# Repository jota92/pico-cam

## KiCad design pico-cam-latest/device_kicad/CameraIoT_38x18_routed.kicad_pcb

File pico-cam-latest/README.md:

# Pico-Cam (Camera IoT)

ESP32-S3 (ESP32-S3-PICO-1-N8R8) をベースにした、超小型・低消費電力の IoT カメラプロジェクトです。ディープスリープを活用し、定期的に JPEG 画像を撮影して Wi-Fi 経由でサーバーにアップロードします。

本リポジトリには、デバイス基板、書き込み・充電用のドック基板の KiCad 回路図・レイアウトデータ、PlatformIO 用のファームウェア、およびアップロード受信用サーバーのサンプルコードが含まれています。

---

## プロジェクト構成

```text
pico-cam/
├── camera_iot/                 # メインの開発・製造パッケージ
│   ├── device_kicad/           # デバイス本体の基板データ (38x18mm 版)
│   ├── cradle_kicad/           # 充電・書き込み用クレードル基板データ (RevA)
│   ├── mechanical/             # デバイスおよびクレードルのレイアウト画像・図面
│   ├── firmware_platformio/    # ESP32-S3 ファームウェア (PlatformIO)
│   ├── server_example/         # アップロード受信用 Express.js サーバー
│   ├── docs/                   # ピンマップや電気設計メモ、DRC レポートなどの設計文書
│   ├── scripts/                # 基板生成や監査用の各種 Python スクリプト
│   ├── jlcpcb_38x18/           # 38x18mm 版の製造用 Gerber/BOM/CPL 出力
│   └── jlcpcb_dock/            # ドック基板の製造用 Gerber/BOM/CPL 出力
├── device_kicad_friend/        # 代替・改良版の基板データ
│   ├── CameraIoT_RevF_40x20_ThroughVia_FINAL.kicad_pcb  # RevF 本体基板 (40x20mm、ブラインドビアなしの通常の4層)
│   ├── CameraIoT_USB-C_Programmer_Dock.kicad_pcb        # USB-C プログラマードック基板
│   └── README_HANDOFF.md       # RevF 基板の製造仕様・引き継ぎドキュメント
├── KiCad/                      # 実行環境用の KiCad 設定 / プロファイル
├── .kicad_cli_profile/         # KiCad CLI 用プロファイル
├── freerouting-1.9.0.jar       # 基板配線用オートルーター (FreeRouting)
└── README.md                   # 本ドキュメント
```

---

## ハードウェア仕様

本プロジェクトには、用途や製造コストに合わせて 2 つの基板バリエーションが存在します。

### 1. デバイス本体基板

*   **ESP32-S3-PICO-1-N8R8**: 8MB Quad Flash & 8MB Octal PSRAM 内蔵モジュール
*   **インターフェース**: カメラモジュール (OV2640 等)、充電検出、ステータス LED、操作ボタン
*   **電源**: LiPo バッテリー接続用コネクタ (J2: JST SH 2ピン)

#### バリエーション:
1.  **38x18mm 版 (`camera_iot/device_kicad/`)**:
    *   極小サイズの設計。
    *   製造用データは `camera_iot/jlcpcb_38x18/` にあります。
2.  **40x20mm RevF 版 (`device_kicad_friend/`)**:
    *   ブラインドビア/埋め込みビアを排除し、通常の「4層貫通ビア (Through-Via)」のみで配線した設計。
    *   JLCPCB などの一般的な基板メーカーで安価に製造可能。
    *   外形寸法: 40.0 x 20.0 mm、基板厚: 0.8 mm。

### 2. 充電・書き込み用ドック (クレードル)

デバイス本体には USB コネクタを搭載せず、外部ドック（ポゴピンまたはケーブル接続）を介して充電やファームウェア書き込みを行います。

*   **Pogo ピンまたは 6-Pin ケーブルインターフェース**:
    1.  `VBUS / VCHG_5V` (電源)
    2.  `GND` (グランド)
    3.  `USB_D+` (native USB D+ / GPIO20)
    4.  `USB_D-` (native USB D- / GPIO19)
    5.  `GPIO0 / BOOT` (書き込みモード遷移用)
    6.  `CHIP_PU / RESET` (チップリセット)
    *   (RevC の pogo 設計では、STAT / WAKE_ID を含めた 8 ポゴピン仕様も存在)

---

## ファームウェア (PlatformIO)

`camera_iot/firmware_platformio/` に格納されているファームウェアは、ESP32-S3 の native USB 機能と Wi-Fi 機能、省電力制御を実装しています。

### ピンアサイン (Pin Map)
*   **PSRAM 競合回避**: ESP32-S3-PICO-1-N8R8 は Octal PSRAM のために `GPIO33~37` を占有するため、カメラのデータラインを `GPIO10-14`、`GPIO38-40` にマッピングして競合を回避しています。
*   **主要ピン**:
    *   `PWDN_GPIO_NUM`: GPIO21
    *   `RESET_GPIO_NUM`: GPIO18
    *   `XCLK_GPIO_NUM`: GPIO15
    *   `SIOD_GPIO_NUM` (SDA): GPIO8
    *   `SIOC_GPIO_NUM` (SCL): GPIO9
    *   `Y2 ~ Y9` (カメラデータ D2~D9): GPIO40, 39, 38, 14, 13, 12, 11, 10
    *   `VSYNC_GPIO_NUM`: GPIO16
    *   `HREF_GPIO_NUM`: GPIO17
    *   `PCLK_GPIO_NUM`: GPIO41
    *   `LED_STATUS_GPIO`: GPIO47 (ステータス LED)
    *   `CHG_DETECT_GPIO`: GPIO4 (充電検出ピン、分圧経由)
    *   `WAKE_BUTTON_GPIO`: GPIO5 (操作・スリープ解除ボタン)
    *   `WAKE_ID_GPIO`: GPIO1 (クレードル接続識別)
    *   `USB_DN_GPIO / USB_DP_GPIO`: GPIO19 / GPIO20 (Native USB デバッグ・書き込み用)

### 主な動作フロー:
1.  **起動**: スリープまたは電源 ON で起動。
2.  **充電検出**: `CHG_DETECT_GPIO` が HIGH の場合（ドックで充電中など）、不要なカメラ撮影や Wi-Fi 接続を行わず、充電に専念するために即座に 1 分間のディープスリープに入ります。
3.  **撮影**: カメラを初期化し、JPEG 画像を取得して PSRAM に格納。
4.  **Wi-Fi 送信**: Wi-Fi に接続し、指定された HTTP サーバへ POST リクエストで画像を送信。
5.  **休止**: 送信完了（またはタイムアウト/エラー）後、ステータス LED をパターン点滅させ、10 分間のディープスリープに入ります。

---

## サーバー (server_example)

`camera_iot/server_example/` は Node.js (Express.js) で書かれたシンプルなアップロード受付サーバーです。

*   **動作**: 送信されてきた Raw JPEG データをトークン認証の上で受信し、日時とランダム文字列のファイル名（例: `2026-06-20T01-23-57-123Z-abcd1234.jpg`）で `./uploads` ディレクトリに保存します。
*   **起動方法**:
    ```bash
    cd camera_iot/server_example
    npm install
    # トークンやポートを指定して起動
    PORT=3000 DEVICE_TOKEN="your-secret-token" node server.js
    ```

---

## 開発と製造に関する注意点

*   **BOM の手配**: LCSC などの自動 PCBA を利用する場合、カメラコネクタや一部の IC など、手作業でのマウント (PCBA 後の手半田) が必要な部品が存在します。詳細は `camera_iot/docs/manual_procurement_revC.md` や `device_kicad_friend/README_HANDOFF.md` をご確認ください。
*   **DRC（デザインルールチェック）**:
    *   RevF 基板は KiCad 10.0.1 の DRC にて、重大なエラー・未配線ともに 0 件であることを確認済みです。

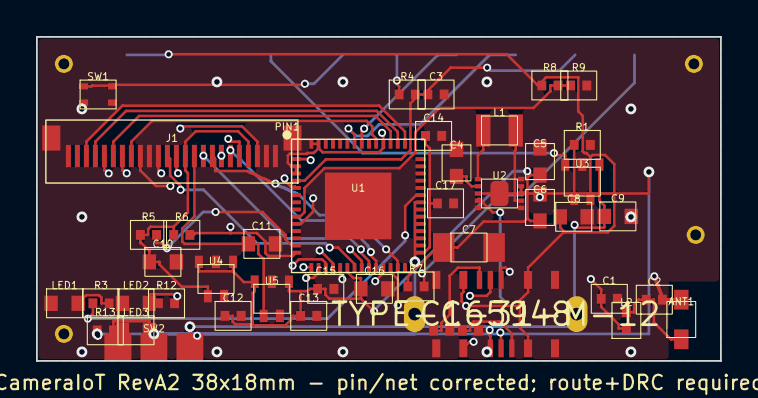
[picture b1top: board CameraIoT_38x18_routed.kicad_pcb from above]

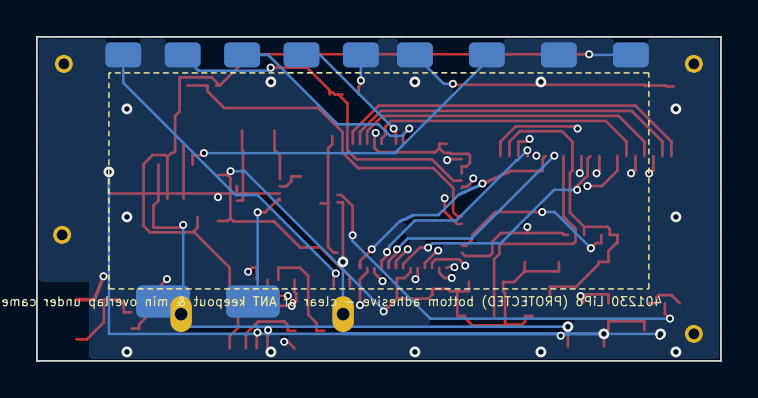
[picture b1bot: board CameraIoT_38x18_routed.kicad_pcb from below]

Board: 4 copper layers, 38.0 x 18.0 mm, 59 parts (11 on the bottom side), 45 nets.

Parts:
ANT1: 2.4GHz chip antenna; ANT_2450AT18B100E
BAT+: BAT+; BATP
BAT-: BAT-; BATN
C1, C2: DNP RF shunt; C_0402_1005Metric
C3, C12, C13: 1uF; C_0402_1005Metric
C4, C5, C6: 10uF 6.3V; C_0603_1608Metric
C7: 47uF 6.3V; C_1206_3216Metric
C8, C10, C16: 10uF; C_0603_1608Metric
C9, C11: 4.7uF; C_0603_1608Metric
C14, C15, C17: 0.1uF; C_0402_1005Metric
J1: OV2640 24pin FPC; FPC_24P_0.5mm_Molex52437-2491
J2: USB-C power+USB2; CameraIoT_USB-C-16P
L1: 1.5uH >=1.5A; IND_2520
L2: 0R/DNP RF series; R_0402_1005Metric
LED1: Blue status LED; LED_0603_1608Metric
LED2: Red Power LED; LED_0603_1608Metric
LED3: Green WiFi LED; LED_0603_1608Metric
MH1: MH1
MH2: MH2
MH3: MH3
MH4: MH4
R1: 20k 1%; R_0402_1005Metric
R3, R12, R13: 1k; R_0402_1005Metric
R4, R5, R6, R7: 10k; R_0402_1005Metric
R8: 68k; R_0402_1005Metric
R9: 100k; R_0402_1005Metric
R10: 5.11k CC1; R_0402
R11: 5.11k CC2; R_0402
SW1: Wake/Boot button; SW_2x1.6mm
SW2: Power Switch
TP1: 5V; BottomPad_5V
TP2: GND; BottomPad_GND
TP3: STAT; BottomPad_STAT
TP4: WAKE; BottomPad_WAKE
TP5: 3V3; BottomPad_3V3
TP6: TX; BottomPad_TX
TP7: RX; BottomPad_RX
TP8: EN; BottomPad_EN
TP9: IO0; BottomPad_IO0
U1: ESP32-S3-PICO-1-N8R8; LGA56_7x7mm_P0.4_PIN1TL
U2: 3.3V buck-boost; VSON10_2.5x2.5_DSK
U3: LiPo charger 4.2V; SOT-23-5
U4: 2.8V LDO; SOT-23-5
U5: 1.3V LDO; SOT-23-5

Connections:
1V3: C11.1, J1.10, U5.5
2V8: C10.1, J1.4, J1.11, R5.1, R6.1, U4.5
3V3: C5.1, C6.1, C7.1, C12.1, C13.1, C15.1, C16.1, R4.1, R7.1, R12.1, TP5.1, U1.2, U1.3, U1.20, U1.46, U1.55, U1.56, U2.8, U2.9, U4.1, U4.3, U5.1, U5.3
CAM_D2: J1.19, U1.45
CAM_D3: J1.21, U1.44
CAM_D4: J1.22, U1.43
CAM_D5: J1.20, U1.19
CAM_D6: J1.18, U1.18
CAM_D7: J1.16, U1.17
CAM_D8: J1.14, U1.16
CAM_D9: J1.12, U1.15
CAM_HREF: J1.9, U1.23
CAM_PCLK: J1.17, U1.47
CAM_PWDN: J1.8, U1.27
CAM_RESETB: J1.6, U1.24
CAM_SIOC: J1.5, R6.2, U1.14
CAM_SIOD: J1.3, R5.2, U1.13
CAM_VSYNC: J1.7, U1.22
CAM_XCLK: J1.13, U1.21
CC1: J2.A5, R10.1
CC2: J2.B5, R11.1
CHG_DETECT: R8.2, R9.1, U1.9
CHG_PROG: R1.1, U3.5
CHG_STAT: TP3.1, U3.1
CHIP_PU: C3.1, R4.2, TP8.1, U1.4
GND: ANT1.2, BAT-.1, C1.2, C2.2, C3.2, C4.2, C5.2, C6.2, C7.2, C8.2, C9.2, C10.2, C11.2, C12.2, C13.2, C14.2, C15.2, C16.2, C17.2, J1.2, J1.15, J1.S1, J1.S2, J2.A1, J2.A12, J2.B1, J2.B12, J2.S1, J2.S2, LED1.1, LED2.1, LED3.1, R1.2, R9.2, R10.2, R11.2, SW1.3, SW1.4, SW2.1, TP2.1, U1.57, U2.5, U2.6, U2.10, U2.11, U3.2, U4.2, U5.2
GPIO0: R7.2, TP9.1, U1.5
LED_A: LED1.2, R3.2
LED_PWR_A: LED2.2, R12.2
LED_STATUS: R3.1, U1.37
LED_WIFI: R13.1, U1.36
LED_WIFI_A: LED3.2, R13.2
LNA_IN: C1.1, L2.1, U1.1
RF_ANT: ANT1.1, C2.1, L2.2
TPS_EN: SW2.2, U2.3
TPS_L1: L1.1, U2.1
TPS_L2: L1.2, U2.7
U0RXD: TP7.1, U1.50
U0TXD: TP6.1, U1.49
USB_DN: J2.A7, J2.B7, U1.25
USB_DP: J2.A6, J2.B6, U1.26
VBAT: BAT+.1, C4.1, C9.1, SW2.3, U2.2, U2.4, U3.3
VCHG_5V: C8.1, J2.A4, J2.A9, J2.B4, J2.B9, R8.1, TP1.1, U3.4
VDD_SPI: C14.1, C17.1, U1.29
WAKE_BUTTON: SW1.1, SW1.2, TP4.1, U1.10

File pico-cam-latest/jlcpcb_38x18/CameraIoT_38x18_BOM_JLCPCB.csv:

Comment,Designator,Footprint,Manufacturer,Manufacturer Part Number,LCSC Part #,Quantity,Notes
2.4GHz chip antenna,ANT1,ANT_2450AT18B100E,Johanson Technology,2450AT18B100E,C2917717,1,JLCPCB SMT
10uF,"C10,C16,C8",C_0603_1608Metric,Samsung,CL10A106MQ8NNNC,C19702,3,JLCPCB SMT
4.7uF,"C11,C9",C_0603_1608Metric,Samsung,CL10A475KO8NNNC,C19666,2,JLCPCB SMT
1uF,"C12,C13,C3",C_0402_1005Metric,Samsung,CL05A105KA5NQNC,C52923,3,JLCPCB SMT
0.1uF,"C14,C15,C17",C_0402_1005Metric,Samsung,CL05B104KO5NNNC,C1525,3,JLCPCB SMT
10uF 6.3V,"C4,C5,C6",C_0603_1608Metric,Samsung,CL10A106MQ8NNNC,C19702,3,JLCPCB SMT
47uF 6.3V,C7,C_1206_3216Metric,Samsung,CL31A476MQHNNNE,C2013,1,JLCPCB SMT
OV2640 24pin FPC,J1,FPC_24P_0.5mm_Molex52437-2491,Molex,52437-2471,C3169564,1,JLCPCB SMT
USB-C power+USB2,J2,CameraIoT_USB-C-16P,,TYPE-C-31-M-12,C165948,1,JLCPCB SMT
1.5uH >=1.5A,L1,IND_2520,Murata,DFE252012F-1R5M=P2,C909806,1,JLCPCB SMT
0R/DNP RF series,L2,R_0402_1005Metric,UNI-ROYAL,0402WGF0000TCE,C17168,1,JLCPCB SMT
Blue status LED,LED1,LED_0603_1608Metric,Everlight,19-21/BHC-ZL1M2VY/3T,C2290,1,JLCPCB SMT
20k 1%,R1,R_0402_1005Metric,UNI-ROYAL,0402WGF2002TCE,C25741,1,JLCPCB SMT
5.11k CC1,R10,R_0402,UNI-ROYAL,0402WGF1001TCE,C21190,1,JLCPCB SMT
5.11k CC2,R11,R_0402,UNI-ROYAL,0402WGF1001TCE,C21190,1,JLCPCB SMT
1k,R3,R_0402_1005Metric,UNI-ROYAL,0402WGF1001TCE,C21190,1,JLCPCB SMT
10k,"R4,R5,R6,R7",R_0402_1005Metric,UNI-ROYAL,0402WGF1002TCE,C25744,4,JLCPCB SMT
68k,R8,R_0402_1005Metric,Yageo,RC0402FR-0768KL,C25907,1,JLCPCB SMT
100k,R9,R_0402_1005Metric,UNI-ROYAL,0402WGF1003TCE,C25803,1,JLCPCB SMT
Wake/Boot button,SW1,SW_2x1.6mm,ALPS Alpine,SKRPACE010,C139797,1,JLCPCB SMT
ESP32-S3-PICO-1-N8R8,U1,LGA56_7x7mm_P0.4_PIN1TL,Espressif,ESP32-S3-PICO-1-N8R8,C7545129,1,JLC SMT/consign
3.3V buck-boost,U2,VSON10_2.5x2.5_DSK,Texas Instruments,TPS63031DSKR,C15516,1,JLCPCB SMT
LiPo charger 4.2V,U3,SOT-23-5,Microchip,MCP73831T-2ACI/OT,C424093,1,JLCPCB SMT
2.8V LDO,U4,SOT-23-5,Texas Instruments,TLV70028DDCR,C507266,1,JLCPCB SMT
1.3V LDO,U5,SOT-23-5,Texas Instruments,TLV70013DDCR,TLV70013DDCR,1,JLC SMT/consign

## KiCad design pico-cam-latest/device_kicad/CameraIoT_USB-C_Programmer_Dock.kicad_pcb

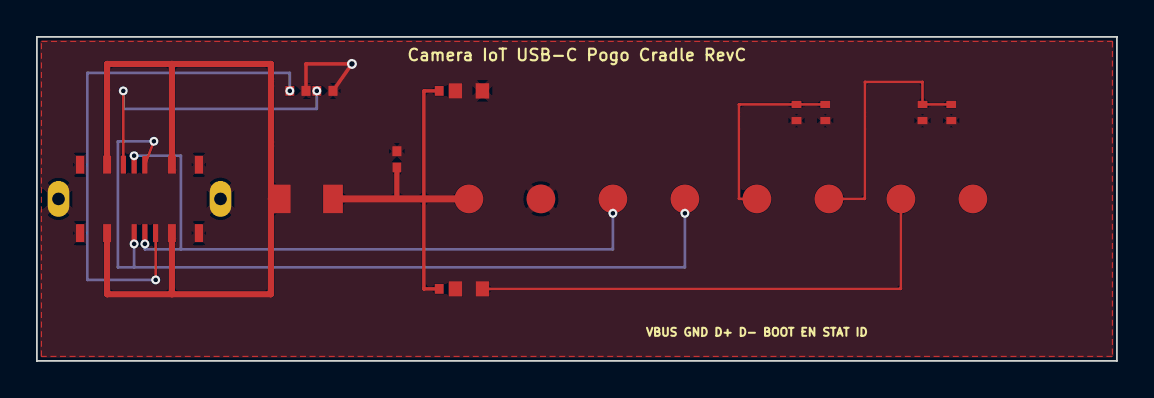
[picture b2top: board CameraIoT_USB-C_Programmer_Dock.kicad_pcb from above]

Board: 2 copper layers, 60.0 x 18.0 mm, 19 parts (0 on the bottom side), 12 nets.

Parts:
D1: 5V TVS; SOD-523
F1: 500mA PTC; Fuse_1206
J1: USB-C power+USB2; CameraIoT_USB-C-16P
LED1: Power LED; LED_0603
LED2: Charge LED; LED_0603
P1: Pogo VBUS; CameraIoT_PogoPad_1.6
P2: Pogo GND; CameraIoT_PogoPad_1.6
P3: Pogo D+; CameraIoT_PogoPad_1.6
P4: Pogo D-; CameraIoT_PogoPad_1.6
P5: Pogo BOOT; CameraIoT_PogoPad_1.6
P6: Pogo RESET; CameraIoT_PogoPad_1.6
P7: Pogo STAT; CameraIoT_PogoPad_1.6
P8: Pogo WAKE/ID; CameraIoT_PogoPad_1.6
R1, R2: 5.1k; R_0402
R3, R4: 2.2k; R_0402
SW2: FLASH button; CameraIoT_SKRPACE010
SW3: RESET button; CameraIoT_SKRPACE010

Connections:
CC1: J1.A5, R1.1
CC2: J1.B5, R2.1
CHG_LED_A: LED2.1, R4.2
CHIP_PU: P6.1, SW3.1, SW3.2
GND: D1.2, J1.A1, J1.A12, J1.B1, J1.B12, J1.S1, J1.S2, LED1.2, P2.1, R1.2, R2.2, SW2.3, SW2.4, SW3.3, SW3.4
GPIO0: P5.1, SW2.1, SW2.2
PWR_LED: LED1.1, R3.2
STAT: LED2.2, P7.1
USB_DN: J1.A7, J1.B7, P4.1
USB_DP: J1.A6, J1.B6, P3.1
VBUS_5V: F1.1, J1.A4, J1.A9, J1.B4, J1.B9
VBUS_PROTECTED: D1.1, F1.2, P1.1, R3.1, R4.1

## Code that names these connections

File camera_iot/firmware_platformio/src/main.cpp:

#include <Arduino.h>
#include <WiFi.h>
#include <HTTPClient.h>
#include "esp_camera.h"

// CameraIoT RevC pin map.
// ESP32-S3-PICO-1-N8R8 reserves GPIO33-37 for octal PSRAM.
// GPIO19/20 are reserved for USB_D-/USB_D+ via the pogo cradle.
// The user button stays on GPIO5; cradle ID is split out to GPIO1.
#define PWDN_GPIO_NUM     21
#define RESET_GPIO_NUM    18
#define XCLK_GPIO_NUM     15
#define SIOD_GPIO_NUM      8
#define SIOC_GPIO_NUM      9
#define Y9_GPIO_NUM       10  // D9 MSB  (was 33 - PSRAM conflict)
#define Y8_GPIO_NUM       11  //         (was 34 - PSRAM conflict)
#define Y7_GPIO_NUM       12  //         (was 35 - PSRAM conflict)
#define Y6_GPIO_NUM       13  //         (was 36 - PSRAM conflict)
#define Y5_GPIO_NUM       14  //         (was 37 - PSRAM conflict)
#define Y4_GPIO_NUM       38
#define Y3_GPIO_NUM       39
#define Y2_GPIO_NUM       40  // D2 LSB
#define VSYNC_GPIO_NUM    16
#define HREF_GPIO_NUM     17
#define PCLK_GPIO_NUM     41

#define LED_STATUS_GPIO   47
#define CHG_DETECT_GPIO    4
#define WAKE_BUTTON_GPIO   5
#define WAKE_ID_GPIO       1
#define USB_DN_GPIO       19
#define USB_DP_GPIO       20

// Fill these in before flashing.
static const char* WIFI_SSID = "YOUR_WIFI_SSID";
static const char* WIFI_PASS = "YOUR_WIFI_PASSWORD";
static const char* UPLOAD_URL = "https://your-server.example.com/upload";
static const char* DEVICE_TOKEN = "replace-with-device-token";

static void blink(int n) {
  pinMode(LED_STATUS_GPIO, OUTPUT);
  for (int i=0; i<n; ++i) { digitalWrite(LED_STATUS_GPIO, HIGH); delay(100); digitalWrite(LED_STATUS_GPIO, LOW); delay(100); }
}

static bool init_camera() {
  camera_config_t config;
  config.ledc_channel = LEDC_CHANNEL_0;
  config.ledc_timer = LEDC_TIMER_0;
  config.pin_d0 = Y2_GPIO_NUM;
  config.pin_d1 = Y3_GPIO_NUM;
  config.pin_d2 = Y4_GPIO_NUM;
  config.pin_d3 = Y5_GPIO_NUM;
  config.pin_d4 = Y6_GPIO_NUM;
  config.pin_d5 = Y7_GPIO_NUM;
  config.pin_d6 = Y8_GPIO_NUM;
  config.pin_d7 = Y9_GPIO_NUM;
  config.pin_xclk = XCLK_GPIO_NUM;
  config.pin_pclk = PCLK_GPIO_NUM;
  config.pin_vsync = VSYNC_GPIO_NUM;
  config.pin_href = HREF_GPIO_NUM;
  config.pin_sccb_sda = SIOD_GPIO_NUM;
  config.pin_sccb_scl = SIOC_GPIO_NUM;
  config.pin_pwdn = PWDN_GPIO_NUM;
  config.pin_reset = RESET_GPIO_NUM;
  config.xclk_freq_hz = 20000000;
  config.pixel_format = PIXFORMAT_JPEG;

  if (psramFound()) {
    config.frame_size = FRAMESIZE_SVGA;  // 800x600 first test. Lower to VGA/QVGA if unstable.
    config.jpeg_quality = 12;
    config.fb_count = 2;
    config.grab_mode = CAMERA_GRAB_LATEST;
  } else {
    config.frame_size = FRAMESIZE_VGA;
    config.jpeg_quality = 14;
    config.fb_count = 1;
    config.grab_mode = CAMERA_GRAB_WHEN_EMPTY;
  }
  config.fb_location = CAMERA_FB_IN_PSRAM;

  esp_err_t err = esp_camera_init(&config);
  if (err != ESP_OK) {
    Serial.printf("Camera init failed: 0x%x\n", err);
    return false;
  }
  sensor_t *s = esp_camera_sensor_get();
  if (s) {
    s->set_framesize(s, FRAMESIZE_VGA); // safer default for first boot
  }
  return true;
}

static bool connect_wifi() {
  WiFi.mode(WIFI_STA);
  WiFi.setSleep(false);
  WiFi.begin(WIFI_SSID, WIFI_PASS);
  uint32_t start = millis();
  while (WiFi.status() != WL_CONNECTED && millis() - start < 12000) {
    delay(200);
    Serial.print('.');
  }
  Serial.println();
  Serial.print("WiFi status: "); Serial.println(WiFi.status());
  return WiFi.status() == WL_CONNECTED;
}

static bool upload_jpeg(camera_fb_t* fb) {
  if (!fb) return false;
  HTTPClient http;
  http.begin(UPLOAD_URL);
  http.addHeader("Content-Type", "image/jpeg");
  http.addHeader("X-Device-Token", DEVICE_TOKEN);
  http.addHeader("X-Device-Name", "camera-iot-revA");
  int code = http.POST(fb->buf, fb->len);
  Serial.printf("HTTP code: %d, bytes: %u\n", code, fb->len);
  String resp = http.getString();
  Serial.println(resp);
  http.end();
  return code >= 200 && code < 300;
}

static void sleep_now() {
  digitalWrite(LED_STATUS_GPIO, LOW);
  WiFi.disconnect(true);
  WiFi.mode(WIFI_OFF);
  esp_sleep_enable_timer_wakeup(10ULL * 60ULL * 1000000ULL); // test: wake every 10 min
  esp_deep_sleep_start();
}

void setup() {
  pinMode(CHG_DETECT_GPIO, INPUT);
  pinMode(WAKE_BUTTON_GPIO, INPUT_PULLUP);
  pinMode(LED_STATUS_GPIO, OUTPUT);
  Serial.begin(115200);
  delay(300);
  Serial.println("CameraIoT RevA boot");

  // If sitting on charger, do not capture or use Wi-Fi. Leave charge current to MCP73831.
  if (digitalRead(CHG_DETECT_GPIO) == HIGH) {
    Serial.println("Charge detected, sleeping.");
    blink(1);
    esp_sleep_enable_timer_wakeup(60ULL * 1000000ULL);
    esp_deep_sleep_start();
  }

  blink(2);
  if (!init_camera()) { blink(5); sleep_now(); }
  camera_fb_t *fb = esp_camera_fb_get();
  if (!fb) { Serial.println("Camera capture failed"); blink(5); sleep_now(); }
  Serial.printf("Captured: %u bytes\n", fb->len);

  bool ok = false;
  if (connect_wifi()) ok = upload_jpeg(fb);
  esp_camera_fb_return(fb);
  blink(ok ? 3 : 6);
  sleep_now();
}

void loop() {}

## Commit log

2026-06-19 Initial commit: Camera IoT hardware design, firmware, and documentation
2026-06-19 Replace repository contents
2026-06-19 include pico-cam-latest contents
